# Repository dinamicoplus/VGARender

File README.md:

# VGA signal generation with PIC24FJ256GA705

This project is dedicated to use the PIC24FJ256GA705 microcontroller for the generation of a VGA video signal. 

## Structure

The repository is structured as follows:
- **src**: Contains all the source code for the microcontroller.
- **nbproject**: Contains all the MPLABX project. That includes all the Makefiles and IDE configuration as well as all the environmental variables definition.
- **PCB_Design/VGA_adapter**: Contains the schematics and PCB design for the VGA Adaptor to be plug in the [PIC24F Curiosity Board](https://www.microchip.com/DevelopmentTools/ProductDetails/DM240004).
- **dithering**: Contains the python scripts that have been used for this project to generate and adapt images to be used in the microcontroller.

### Releases

**[VGA Render Project v0.2](https://github.com/dinamicoplus/VGARender/releases/tag/v0.2)**

## Installing and compilation

This project has been created using [MPLABX X IDE](https://www.microchip.com/mplab/mplab-x-ide) from Microchip. To compile the project and flash it into the [PIC24F Curiosity Board](https://www.microchip.com/DevelopmentTools/ProductDetails/DM240004), download **nbproject** and **src** into the same folder. Then MPLAB X IDE will detect this as a MPLAB project and set it as an active project. From there, there is two configurations available:
- *PIC24FJ256GA705_SIM*: This is the configuration for the simulation of the project. It has the same setting as the configuration for the target. Use this to simulate the project in your computer without the actual hardware.
- *PIC24FJ256GA705_TARGET*: This is the configuration for the target. It has been set to work with the PIC24F Curiosity Board, that is, for the use of PKOB Starter Kit Debugger. You can use another flasher or debugger to work with. This is the one that I have used.

## Specifications

The system aims to generate a VGA video signal but the microcontroller used can only be set to run at 16 MIPS (32 MHz). With that limitation on mind, the system has the following specifications:
- 150 x 96 pixel resolution
- [3-bit RGB palette](https://en.wikipedia.org/wiki/List_of_monochrome_and_RGB_palettes#3-bit_RGB)
- Only ~8% of CPU time available, as the rest of the time is used to generate the signal.
- Certain level of asynchronism, as the lowest frequency VGA signal is spected to have 25.175 MHz as pixel frecuency. However, this can be compensated if the TV Monitor used is modern.

In spite all these limitations, **an implementation of [Conway's Game of Life](https://en.wikipedia.org/wiki/Conway%27s_Game_of_Life)** has been achieved.
The project has the *user.c* and *user.h* files to be used by the user to define the function that he wants. Currently it implements the game [Conway's Game of Life](https://en.wikipedia.org/wiki/Conway%27s_Game_of_Life) as a demonstration. However this can be changed at discretion.

## Auxiliary tools

The project includes a python script with functions that can be used to generate a header file for the definition pixel C array. In order to use them the following dependencies needs to be installed:

- Python3
- PIL

Help can be found invoking the following command:

```bash
> python3 img_dith.py -h
usage: img_dith.py [-h] [-o O] [-width WIDTH] [-height HEIGHT] [-bits BITS]
                   [-header HEADER]
                   input

Process dithering to picture

positional arguments:
  input           input picture

optional arguments:
  -h, --help      show this help message and exit
  -o O            output picture
  -width WIDTH    width of the pic
  -height HEIGHT  heigth of the pic
  -bits BITS      bit depth of the pic
  -header HEADER  output header
```
    
Take into account that the script as is will process the image using the [Flos-Steinberg dithering](https://en.wikipedia.org/wiki/Floyd%E2%80%93Steinberg_dithering) algorithm. In order to disable the dithering, modify the following line in *img_dith.py*:

```python
# Process the image. Resize, Floyd–Steinberg dithering or Posterize
img = Image.open(in_img)
img = resize_wo_deform(img,(w,h))
#img = posterize(img, bit_depth) <-- Uncomment this line
img = fs_dithering(img,bit_depth) #<-- Comment this line
```

## PCB VGA Adaptor

The project requires to manufacture an VGA adaptor for the PIC24F Curiosity Board. The signals are mapped as following:

| uC Pin   | VGA Signal    |  DB15 Pin |
|----------|---------------|-----------|
| RA0      | RED           | 1         |
| RA1      | GREEN         | 2         |
| RA2      | BLUE          | 3         |
| RB7      | H_SYNC        | 13        |
| RB9      | V_SYNC        | 14        |

For the proposed design go to the **PCG_Design** folder. This PCB can be plug into the PIC24F Curiosity board.

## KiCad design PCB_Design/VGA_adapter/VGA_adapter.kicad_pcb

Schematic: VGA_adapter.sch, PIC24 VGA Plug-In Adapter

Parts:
J1: VGA Output; DSUB-15-HD_Female_Horizontal_P2.29x1.98mm_EdgePinOffset3.03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
J2: PIC24 Curiosity Board Adapter; 2xPinHeader_2x14_P2.54mm_Vertical
R1, R2, R3: 470; R_0805_2012Metric

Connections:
BLUE: J1.3 (BLUE), R2.2
GND: J1.6 (GND_R), J1.7 (GND_G), J1.8 (GND_B), J1.10 (GND_SYNC), J2.2 (GND), J2.11 (GND), J2.20 (GND), J2.28 (GND), J2.30 (GND), J2.39 (GND), J2.47 (GND)
GREEN: J1.2 (GREEN), R3.2
H_SYNC: J1.13 (H_SYNC), J2.6 (RB7)
unnamed: J2.43 (RA2), R2.1
unnamed: J2.55 (RA1), R3.1
unnamed: J2.56 (RA0), R1.2
RED: J1.1 (RED), R1.1
V_SYNC: J1.14 (V_SYNC), J2.8 (RB9)

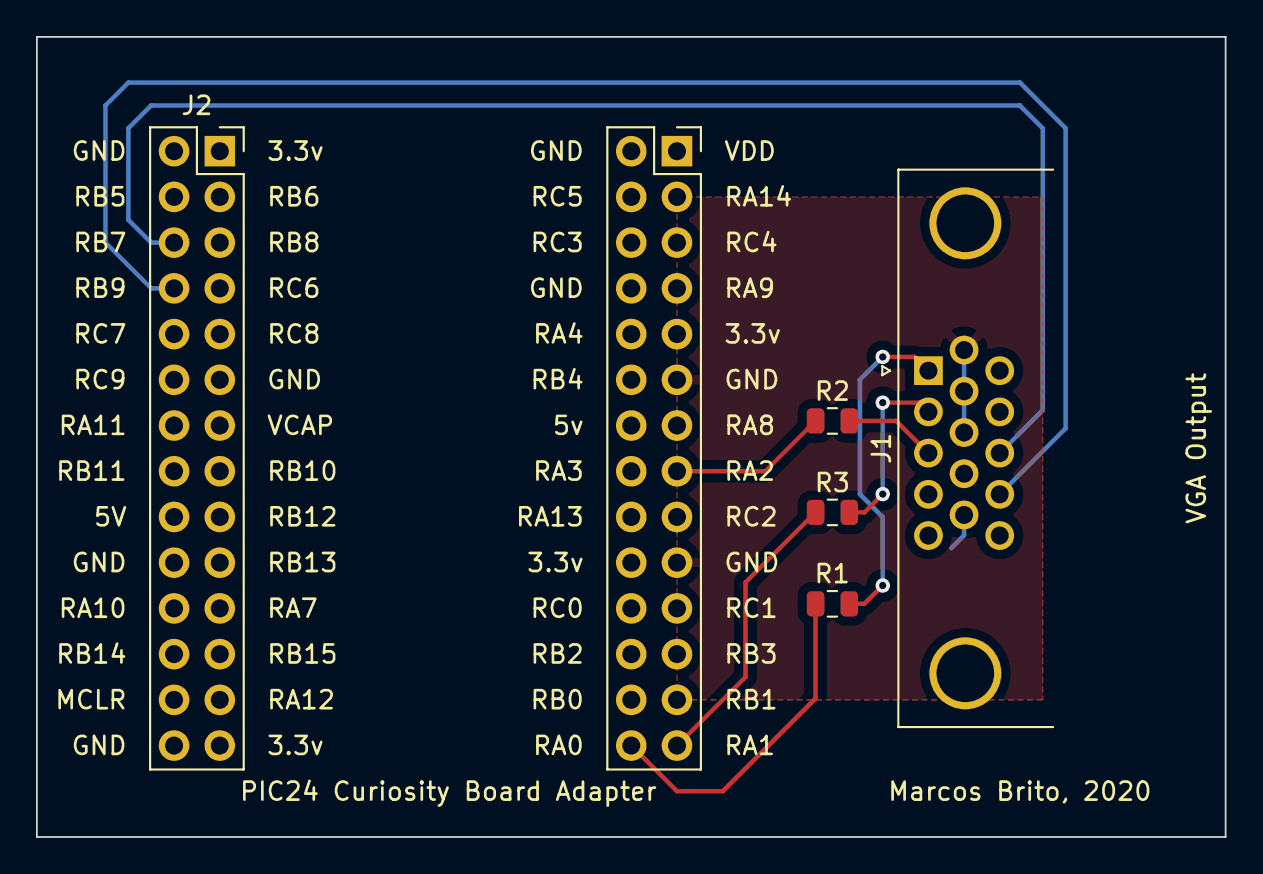
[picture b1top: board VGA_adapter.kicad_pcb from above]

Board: 2 copper layers, 66.0 x 44.5 mm, 5 parts (0 on the bottom side), 9 nets.

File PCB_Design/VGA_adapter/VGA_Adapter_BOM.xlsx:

Comment | Designator | Footprint | LCSC Part #（optional）
470Ohm | R1, R2, R3 | 0805_R | C17710

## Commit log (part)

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2020-01-19 Init commit
2020-01-19 CCP1 configured with interreptions
2020-01-19 Added assambly code in CCP1 interruption
2020-01-19 Create one assambly code file and add one CCP interruption to it
2020-01-27 Add configuration for target. Add interruption managed with assembler
2020-04-26 Change CLK config to FRCPLL 32MHz
2020-04-26 Add a first approach to vertical line implementation
2020-05-05 Add first PCB design for PIC24 VGA adaptor
2020-05-15 First version of PCB adapter
2020-05-15 Complete first version of VGARender Project
2020-05-15 Add script to create an array from dithered image
2020-05-15 Improve efficiency thus resolution to 150x96 pixels
2020-05-15 Implement first animation
2020-05-16 Add frame period variable controlled by knob
2020-05-16 Rewrite user.c as state machine logic
2020-05-17 Added multiple states for transition list, and changed into double array
2020-05-17 Change folder structure
2020-05-17 Refactor python dithering script with comments and new functions
2020-05-17 Refactor all src files and add documentation per each file
2020-06-29 PCB_Design: Add resistors to .sch and 3D model for pins
